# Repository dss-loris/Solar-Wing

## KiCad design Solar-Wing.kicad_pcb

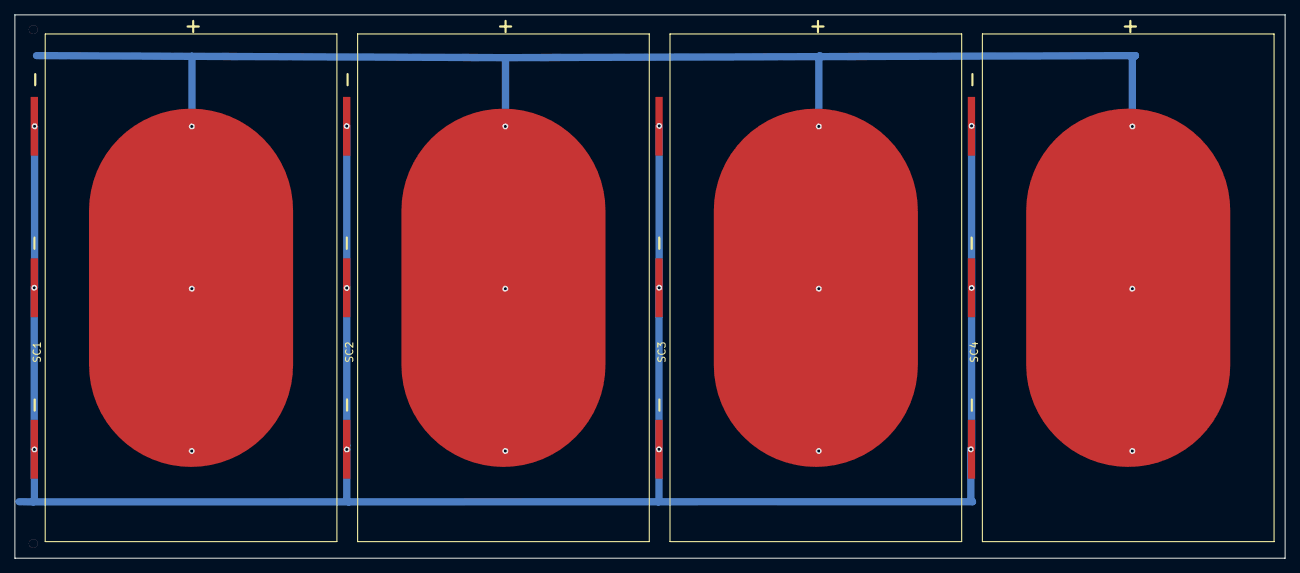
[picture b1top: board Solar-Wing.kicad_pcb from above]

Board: 2 copper layers, 173.0 x 74.0 mm, 4 parts (0 on the bottom side), 2 nets.

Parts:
SC1, SC2, SC3, SC4: Solar_Cell; XTJ Prime

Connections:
+: SC1.1, SC2.1, SC3.1, SC4.1
-: SC1.2, SC2.2, SC3.2, SC4.2

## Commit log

2020-05-15 Added basic schematic for later netlist and added empty project footprint library
2020-05-19 Added footprint for XJT Prime solar cell
2020-05-24 PCB V1
2020-05-31 Updated XTJ Prime footprint
